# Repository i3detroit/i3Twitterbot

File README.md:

i3Twitterbot
============

Twitterbot!

Features
========
* Near-realtime switch status
* Countdown timer for picture grab
* Prominent on/off LEDs
* Twitter/Twitpic integration
* IRC integration
* Website integration

Requirements
============
* [tweepy](http://github.com/tweepy/tweepy)
	- setuptools
	- [py_compile](https://groups.google.com/forum/?fromgroups=#!topic/beaglebone/LU6LoEs-zHQ) (missing on the beaglebone Angstrom -.-)
* [oyoyo](https://code.google.com/p/oyoyo/)
* [py-spi](http://www.gigamegablog.com/2012/09/09/beaglebone-coding-101-spi-output/)
* [PyBBIO](https://github.com/alexanderhiam/PyBBIO)
* [ivy-python](http://www.eei.cena.fr/products/ivy/download/checkouts.html)
* [paramiko](https://github.com/paramiko/paramiko/)

Usage
=====
0. Have beaglebone running Angstrom with custom cape and hardware.
1. Edit `twitterbot.ini.example` for your installation parameters.
2. Make sure to rename `twitterbot.ini.example` to `twitterbot.ini`.
3. Start up `manager.py`, which should start up all the other agents.

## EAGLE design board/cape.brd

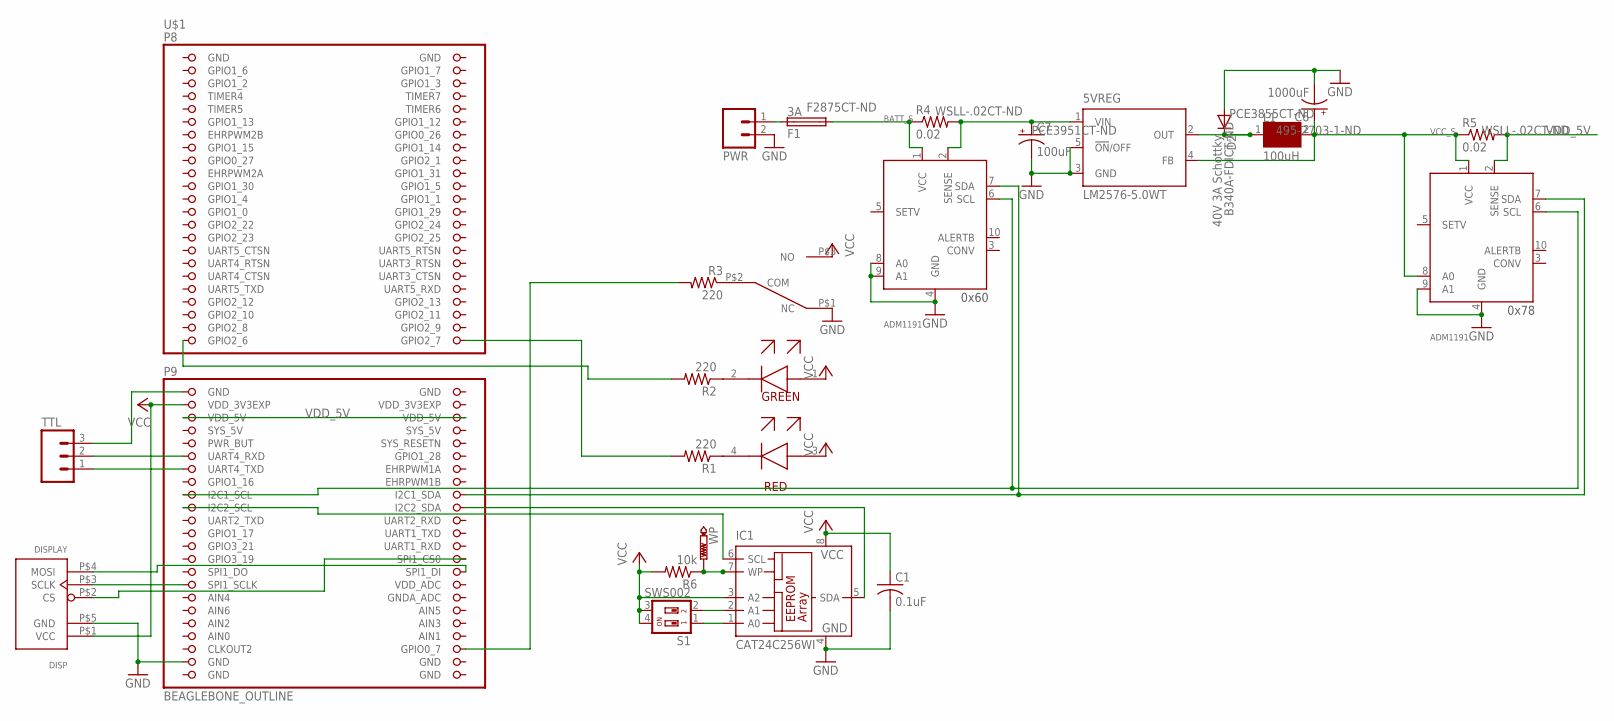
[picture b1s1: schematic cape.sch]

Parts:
5VREG: LM2576-5.0WT; TO263-5
BATT_S: ADM1191; MSOP-10
C1: 0.1uF; C0603
C6: 1000uF; 175TMP-0808; DIGIKEY PCE3855CT-ND
C7: 100uF; 153CLV-0605; DIGIKEY PCE3951CT-ND
D2: 40V 3A Schottky; DO-214AC; DIGIKEY B340A-FDICT-ND
DISP: DISPLAY; 1X6
F1: 3A; 2920; DIGIKEY F2875CT-ND
IC1: CAT24C256WI; SO-08
L1: 100uH; INDUCTOR; DIGIKEY 495-2703-1-ND
PWR: M025MM; SCREWTERMINAL-5MM-2
R1, R2, R3: 220; R0603
R4, R5: 0.02; R0603; DIGIKEY WSLL-.02CT-ND
R6: 10k; R0603
S1: SWS002; SMS-002
TTL: M03LOCK; 1X03_LOCK
U$1: BEAGLEBONE_OUTLINE; BEAGLEBONE_SHIELD
U$2: LEDS; 2X2
U$3: SWITCH; 1X3
VCC_S: ADM1191; MSOP-10
WP: PTR1TP10R; TP10R

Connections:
12VDC: F1.1, PWR.1
12V_FUSE: 5VREG.1 (VIN), BATT_S.2 (SENSE), C7.+, R4.2
AIN0: U$1.85 (AIN0)
CS: DISP.P$2 (CS), U$1.74 (SPI1_CS0)
GND: 5VREG.3 (GND), 5VREG.5 (!ON!/OFF), BATT_S.4 (GND), BATT_S.8 (A0), BATT_S.9 (A1), C1.2, C6.-, C7.-, D2.A, DISP.P$5 (GND), IC1.4 (GND), PWR.2, TTL.3, U$1.1 (GND), U$1.2 (GND), U$1.47 (GND), U$1.48 (GND), U$1.89 (GND), U$1.90 (GND), U$1.91 (GND), U$1.92 (GND), U$3.P$1 (NC), VCC_S.4 (GND), VCC_S.9 (A1)
GRN_LED: R2.2, U$1.45 (GPIO2_6)
I2C1_SCL: BATT_S.6 (SCL), U$1.63 (I2C1_SCL), VCC_S.6 (SCL)
I2C1_SDA: BATT_S.7 (SDA), U$1.64 (I2C1_SDA), VCC_S.7 (SDA)
I2C2_SCL: IC1.6 (SCL), U$1.65 (I2C2_SCL)
I2C2_SDA: IC1.5 (SDA), U$1.66 (I2C2_SDA)
unnamed: R1.1, U$2.4
unnamed: R2.1, U$2.2
unnamed: R3.1, U$3.P$2 (COM)
unnamed: DISP.P$4 (MOSI), U$1.76 (SPI1_DI)
unnamed: 5VREG.2 (OUT), D2.C, L1.1
unnamed: BATT_S.1 (VCC), F1.2, R4.1
unnamed: IC1.1 (A0), S1.1
unnamed: IC1.2 (A1), S1.2
unnamed: 5VREG.4 (FB), C6.+, L1.2, R5.1, VCC_S.1 (VCC), VCC_S.8 (A0)
unnamed: IC1.7 (WP), R6.1, WP.TP
RED_LED: R1.2, U$1.46 (GPIO2_7)
RXI: TTL.2, U$1.57 (UART4_RXD)
SCLK: DISP.P$3 (SCLK), U$1.77 (SPI1_SCLK)
SW: R3.2, U$1.88 (GPIO0_7)
SYS_5V: U$1.53 (SYS_5V)
TXO: TTL.1, U$1.59 (UART4_TXD)
VCC: C1.1, DISP.P$1 (VCC), IC1.3 (A2), IC1.8 (VCC), R6.2, S1.3, S1.4, U$1.49 (VDD_3V3EXP), U$2.1, U$2.3, U$3.P$3 (NO)
VDD_3V3EXP: U$1.50 (VDD_3V3EXP)
VDD_5V: R5.2, U$1.51 (VDD_5V), U$1.52 (VDD_5V), VCC_S.2 (SENSE)

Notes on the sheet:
0x78
0x60

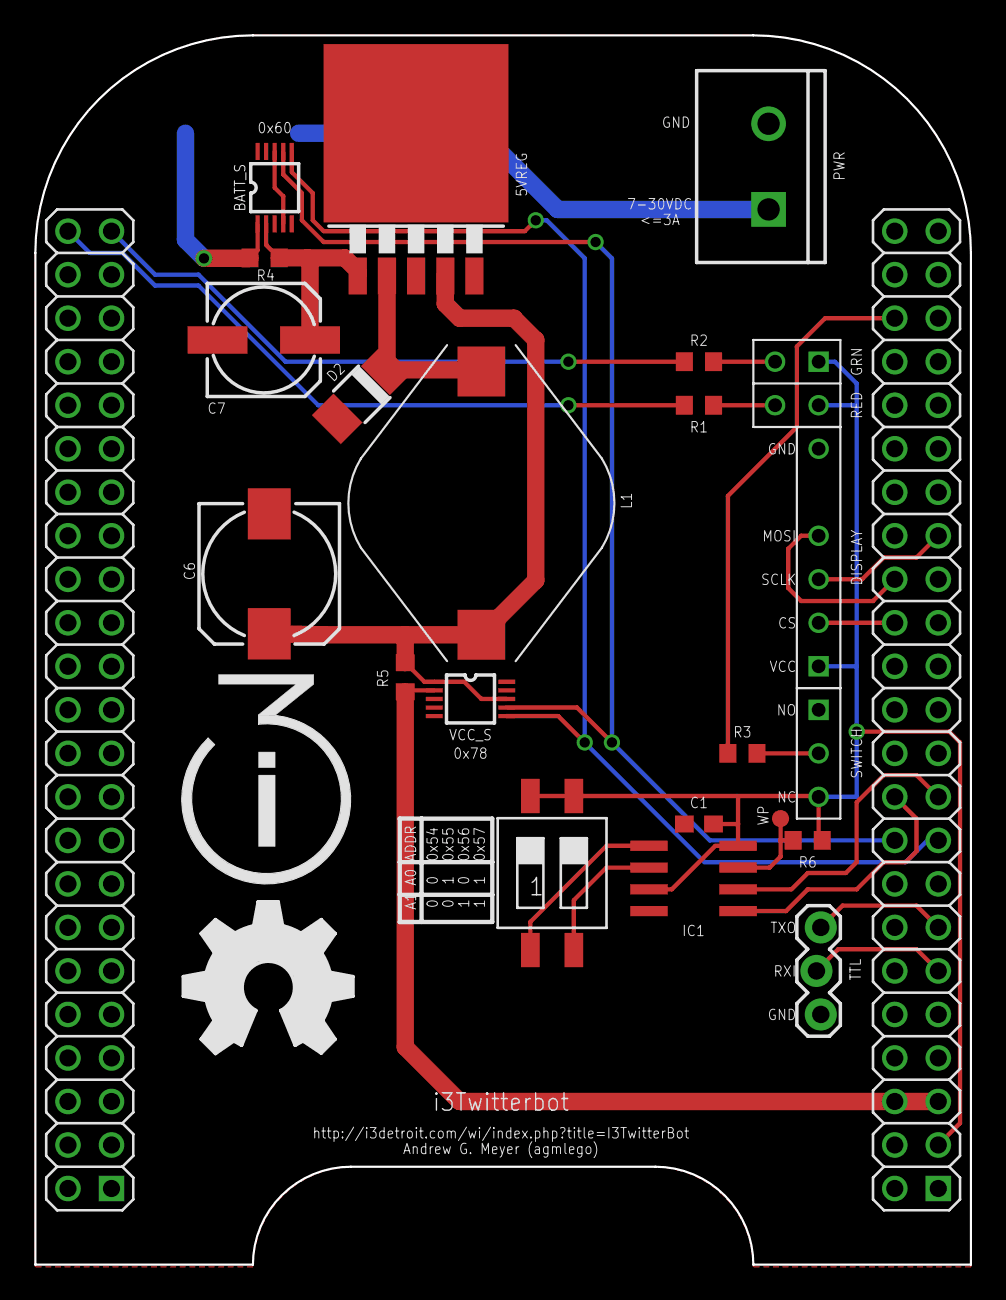
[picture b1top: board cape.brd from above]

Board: 2 copper layers, 54.6 x 71.8 mm, 25 parts (1 on the bottom side), 26 nets.

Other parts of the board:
U$4: OSHW_FILLX350_NOTEXT

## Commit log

2012-09-12 Edited README
2013-05-09 Working IRC base from phenny.
2013-06-13 Something changed in the Phenny Twitter module.
2013-06-13 Added driver for PT6961 controller on 4-digt seven-segment display, using py-spi. Does not seem to work yet...
2013-06-13 Debugging...py-spi does not actually accomplish lsbfirst successfully
2013-06-30 Switching from phenny to oyoyo.
2013-07-06 Added board files, moved code to subdirectory.
2013-07-06 Added code example to pull JPG data off IP camera.
2013-07-07 Finished schematic and routing.
2013-07-07 Moved items on tDocu to _tsilk for OSHPark.
2013-07-07 Added project information and logos to board.
2013-07-08 Moved i3 logo to _tsilk after tracing by hand...hopefully it shows up in OSHPark now.
2013-09-24 Added code for interrupt-based switch response and LED control.
2013-09-24 Moved hardware stuff into code directory. Added cape-specific information.
2013-09-25 Added requirement for ivy-python.
2013-09-25 Added auth and join commands to irc module
2013-09-25 Official changeover from phenny to oyoyo. IRC side appaears to be functional.
2013-09-25 Edited hardware script to use Ivy and announce status whenever one of the dependent clients shows up or on request or hardware state change.
2013-09-26 Added config file (generator script forthcoming) to store things like IRC connection details, log levels, and Twitter OAuth tokens.
2013-09-26 Initial draft of tweepy-powered update script. Modeled after the IRC module, but with Twitter updates instead of channel announcements.
2013-09-26 Renamed twitter module to avoid name collision with tweepy module.
2013-09-26 IRC, hardware, and Twitter modules use config file, removed directories to make deployment and operation simpler.
2013-11-01 Syntax fixes and style
2013-12-28 Changed switch pin due to conflicts with boot-configuration pins.
2013-12-29 Fixed failures to send status changes to Ivy bus, agent name/interested parties list.
2013-12-29 Added logic for demo mode, showing off time, date, and countdown sequence.
2013-12-29 Added bash file to mux UART4 correctly for OAC interface.
2013-12-29 Altered board to as-built greenwiring, fixing confusion on SPI1_D0/SPI1_D1 and moving the switch from a necessary boot-configuration pin to a free one.
2013-12-30 Added agent for website update. Currently uses SFTP to push a file to be included by hacky Wordpress/PHP script. Should use SpaceAPI or similar; later project.
2013-12-30 Added sample INI file for configuartion.
2013-12-30 Added camera functionality. Image will be pushed to same webserver as space-status file for hacky Wordpress/PHP script to grab. Hello, Internet\!
2013-12-30 Added camera to list of interested agents in switch notices.
2013-12-30 Added countdown to camera.
2013-12-30 Finalised fixes before rollout.
2013-12-31 Altered logging system to be config-file-based, and moved config files to separate directory.
2013-12-31 Added rate-limiting to interrupt.py, closing #1
2013-12-31 Added image-upload capability to Twitter agent, resolves #2.
2013-12-31 Added manager.py script, resolves #5.
2013-12-31 Fixed crash bug in twitter.py
2014-01-02 Resolves #6.
2014-01-04 irc.py now checks in announce channels to see if it can change the topic instead of announcing in-band. Added logic for agents to poll interrupt.py for switch state. Resolves #7.
2014-01-04 Fixed initialisation routines for switch status.
2014-08-15 Minor changes to manager.py

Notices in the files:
parts and their libraries:
SparkFun: Licensing: CC v3.0 Share-Alike You are welcome to use this library for commercial purposes.
